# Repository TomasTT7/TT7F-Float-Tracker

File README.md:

# TT7F-Float-Tracker

This is the main repository for [TT7F high altitude balloon tracker](http://tt7hab.blogspot.cz/2016/08/the-tt7f-hardware.html).
It includes the board and schematic Eagle files and the current state of software that is continually being worked on.

The tracker is designed around Atmel's SAM3S8B microcontroller. It acquires the current position from Ublox MAX-M8Q GPS module. As a transmitter it uses Silicon Labs Si4060 to transmit in the 70cm and 2m bands. It is also equipped with a connector and an interface for MT9D111 camera module to provide [SSDV](https://ukhas.org.uk/guides:ssdv) (Slow Scan Digital Video) capability.

The power supply consists of TPS63031 buck-boost converter providing 3.3V to the MCU, GPS module and transmitter. The MT9D111 camera module is powered by two ME6211 LDO regulators (1.8V and 2.8V). The tracker is also capable of using LTC3105 MPPC converter in connection with a pair of solar cells to charge a battery (up to 4.2V) and power the TPS63031 converter.

For programming purposes it is equipped with a USB micro B interface which can provide power to the board via MCP1700 LDO regulator as well.

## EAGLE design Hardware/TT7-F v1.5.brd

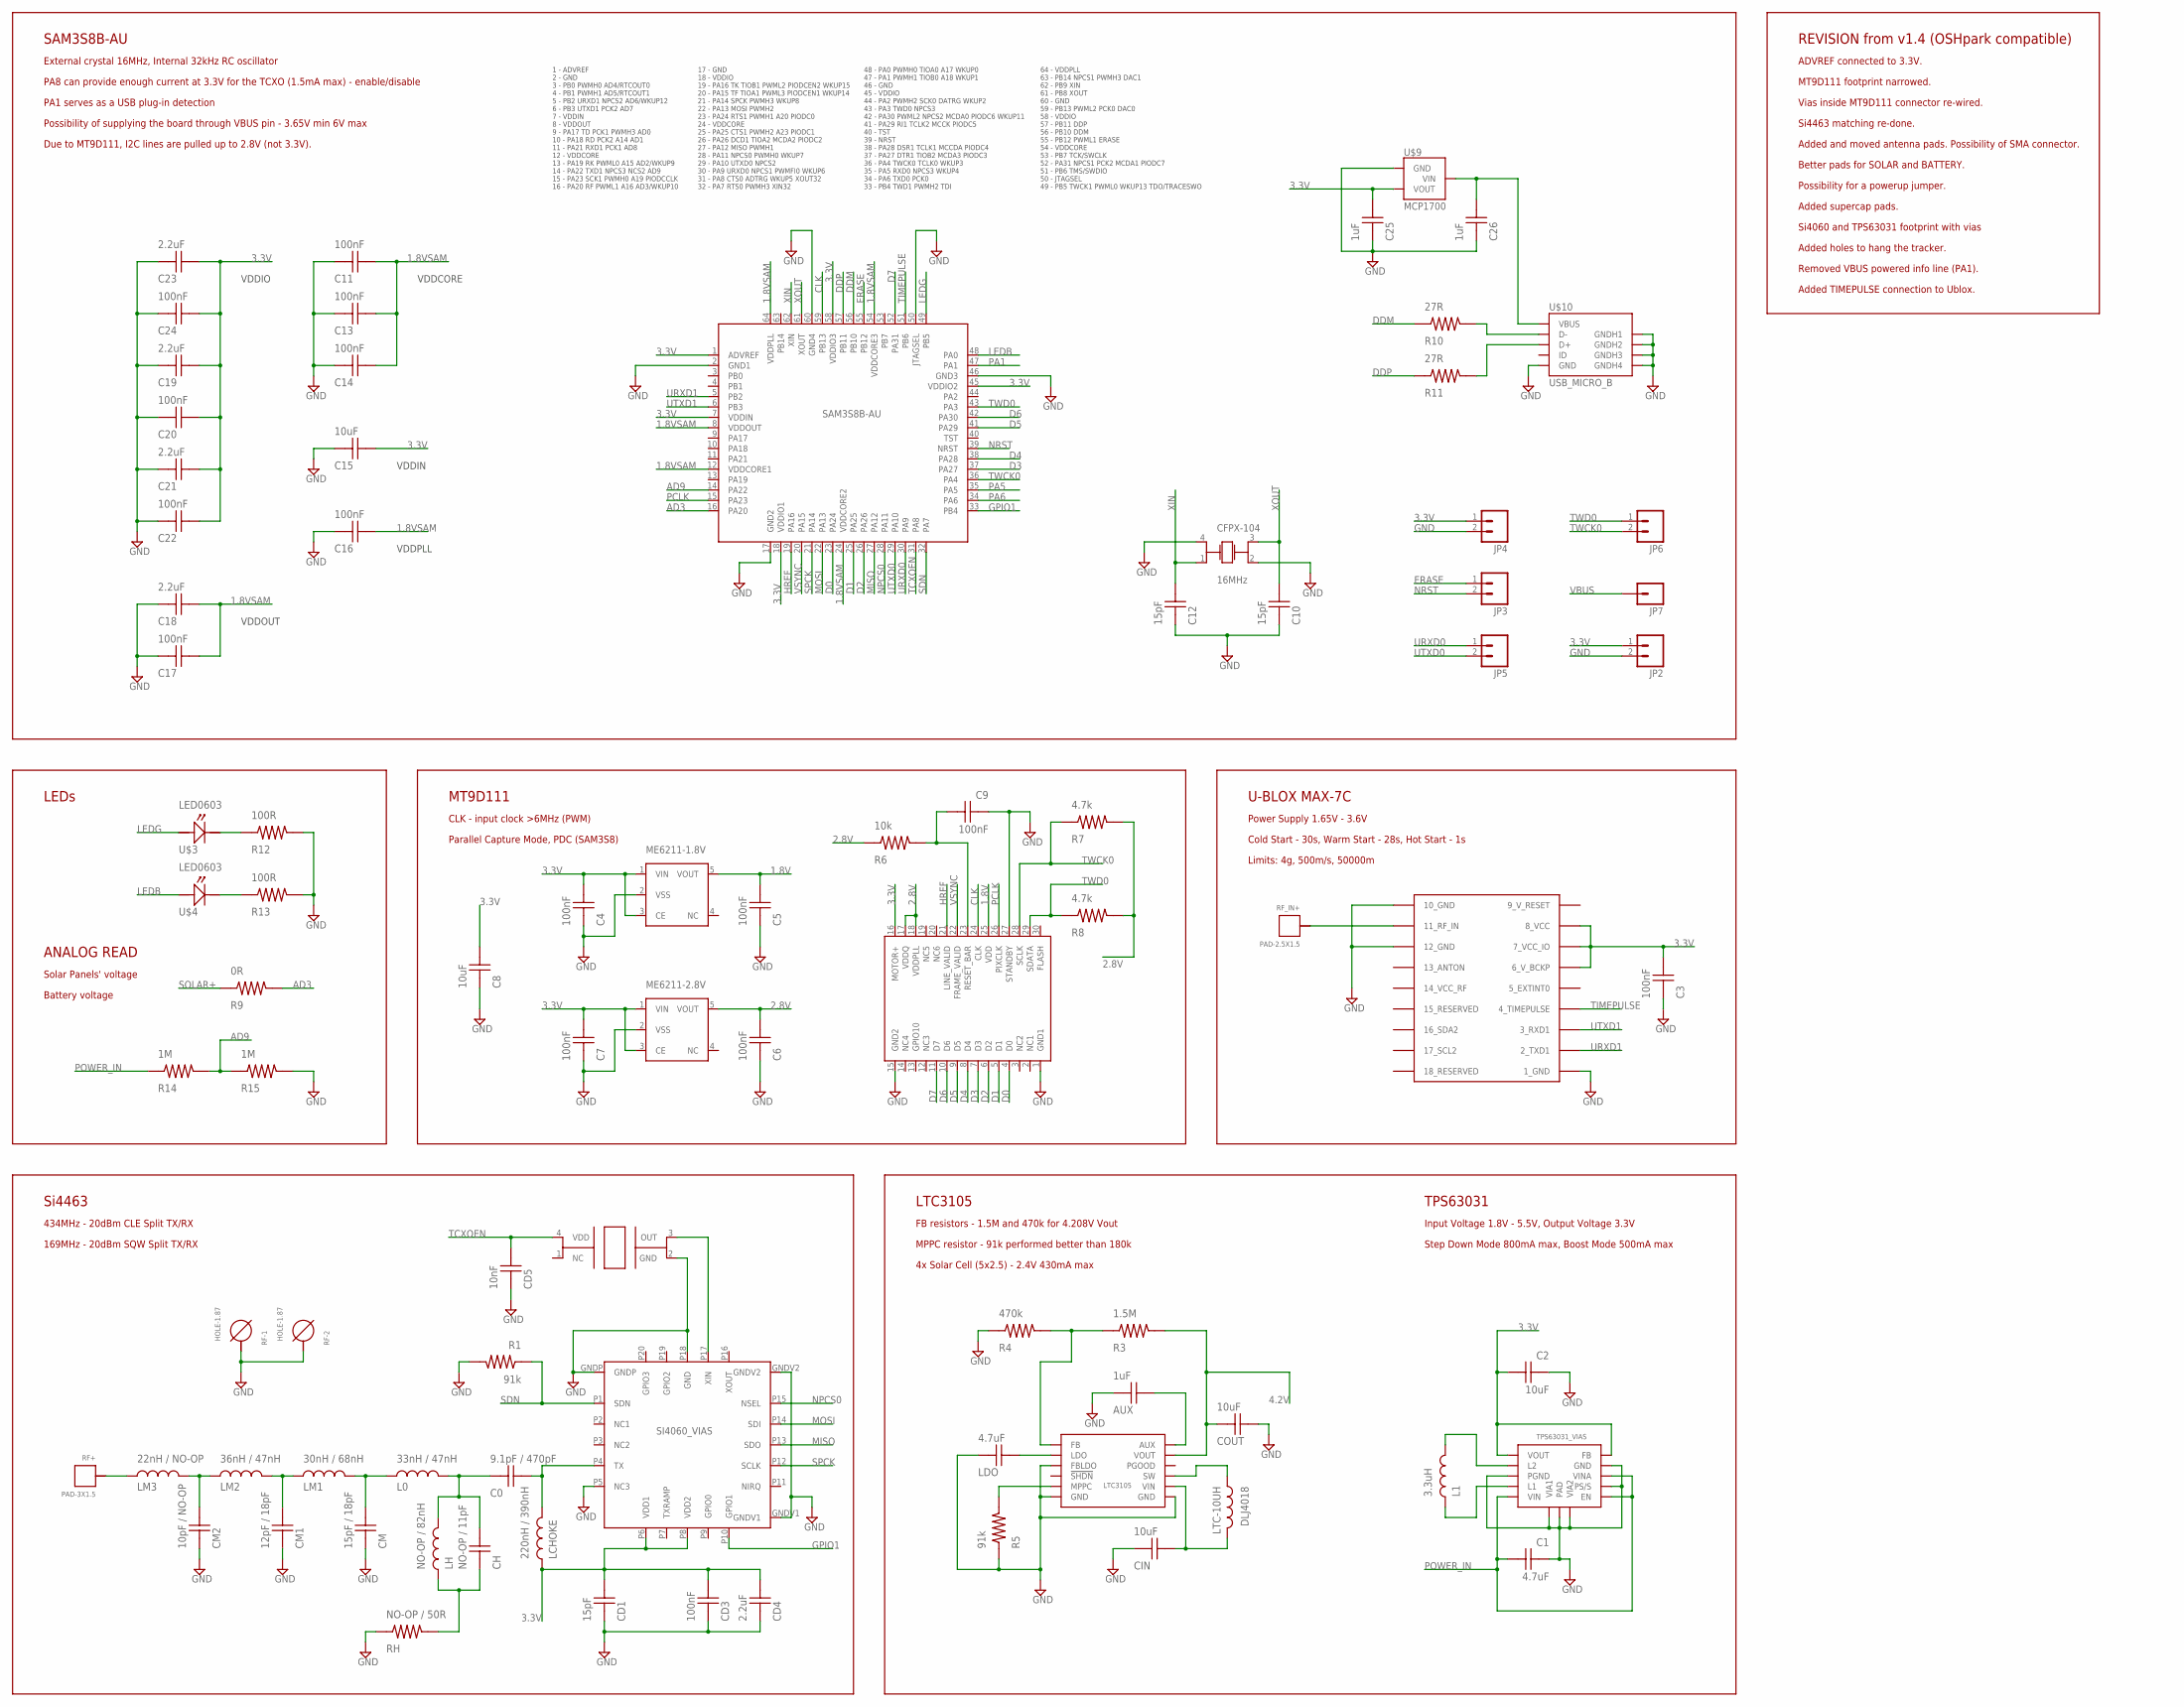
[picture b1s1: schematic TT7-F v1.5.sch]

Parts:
AUX: 1uF; CAP0603
C0: 9.1pF / 470pF; CAP0402
C1: 4.7uF; CAP0603
C2, C8: 10uF; CAP0805
C3, C4, C5, C6, C7, C9, C11, C13, C14, C16, C17, C20, C22, C24: 100nF; CAP0402
C10, C12: 15pF; CAP0402
C15: 10uF; CAP0603
C18, C19, C21, C23: 2.2uF; CAP0402
C25, C26: 1uF; CAP0603
CD1: 15pF; CAP0402
CD3: 100nF; CAP0402
CD4: 2.2uF; CAP0402
CD5: 10nF; CAP0402
CFPX-104: 16MHz; CFPX-104
CH: NO-OP / 11pF; CAP0402
CIN: 10uF; CAP0603
CM: 15pF / 18pF; CAP0402
CM1: 12pF / 18pF; CAP0402
CM2: 10pF / NO-OP; CAP0402
COUT: 10uF; CAP0805
JP2, JP3, JP4, JP5, JP6: M021X02_NO_SILK; 1X02_NO_SILK
JP7: M01PTH_NO_SILK_YES_STOP; 1X01_NO_SILK
L0: 33nH / 47nH; IND0402
L1: 3.3uH; DLJ3015
LCHOKE: 220nH / 390nH; IND0402
LDO: 4.7uF; CAP0603
LH: NO-OP / 82nH; IND0402
LM1: 30nH / 68nH; IND0402
LM2: 36nH / 47nH; IND0402
LM3: 22nH / NO-OP; IND0402
LTC-10UH: DLJ4018
ME6211-1.8V, ME6211-2.8V: ME6211_NEW
R1, R5: 91k; RES0402
R3: 1.5M; RES0402
R4: 470k; RES0402
R6: 10k; RES0402
R7, R8: 4.7k; RES0402
R9: 0R; RES0402
R10, R11: 27R; RES0402
R12, R13: 100R; RES0402
R14, R15: 1M; RES0603
RF+: PAD-3X1.5
RF-1, RF-2: HOLE-1.87
RF_IN+: PAD-2.5X1.5
RH: NO-OP / 50R; RES0402
TCXO: 32MHz; I547-2P3_TCXO
U1: LTC3105
U3: TPS63031_VIAS
U4: SAM3S8B-AU
U$1: SI4060_VIAS
U$2: UBLOX_MAX-7C
U$3, U$4: LED0603
U$9: MCP1700
U$10: USB_MICRO_B
U$15: MT9D111-AVX145602-NEW

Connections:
1.8V: C5.P$2, ME6211-1.8V.5 (VOUT), U$15.25 (VDD)
1.8VSAM: C11.P$2, C13.P$2, C14.P$2, C16.P$2, C17.P$2, C18.P$2, U4.8 (VDDOUT), U4.12 (VDDCORE1), U4.24 (VDDCORE2), U4.54 (VDDCORE3), U4.64 (VDDPLL)
2.8V: C6.P$2, ME6211-2.8V.5 (VOUT), R6.P$1, R7.P$2, R8.P$2, U$15.17 (VDDQ), U$15.18 (VDDPLL)
3.3V: C2.P$2, C3.P$2, C4.P$2, C7.P$2, C8.P$2, C15.P$2, C19.P$2, C20.P$2, C21.P$2, C22.P$2, C23.P$2, C24.P$2, C25.P$2, CD1.P$2, CD3.P$2, CD4.P$2, JP2.1, JP4.1, LCHOKE.P$1, ME6211-1.8V.1 (VIN), ME6211-1.8V.3 (CE), ME6211-2.8V.1 (VIN), ME6211-2.8V.3 (CE), U3.1 (VOUT), U3.10 (FB), U4.1 (ADVREF), U4.7 (VDDIN), U4.18 (VDDIO1), U4.45 (VDDIO2), U4.58 (VDDIO3), U$1.P6 (VDD1), U$1.P8 (VDD2), U$2.6_V_BCKP, U$2.7_VCC_IO, U$2.8_VCC, U$9.2 (VOUT), U$15.16 (MOTOR+)
4.2V: COUT.P$1, R3.P$2, U1.11 (VOUT)
9_V_RESET: U$2.9_V_RESET
AD3: R9.P$2, U4.16 (PA20)
AD9: R14.P$2, R15.P$1, U4.14 (PA22)
CLK: U4.59 (PB13), U$15.24 (CLK)
D0: U4.23 (PA24), U$15.4 (D0)
D1: U4.25 (PA25), U$15.5 (D1)
D2: U4.26 (PA26), U$15.6 (D2)
D3: U4.37 (PA27), U$15.7 (D3)
D4: U4.38 (PA28), U$15.8 (D4)
D5: U4.41 (PA29), U$15.9 (D5)
D6: U4.42 (PA30), U$15.10 (D6)
D7: U4.52 (PA31), U$15.11 (D7)
DDM: R10.P$1, U4.56 (PB10)
DDP: R11.P$1, U4.57 (PB11)
ERASE: JP3.1, U4.55 (PB12)
GND: AUX.P$1, C1.P$1, C2.P$1, C3.P$1, C4.P$1, C5.P$1, C6.P$1, C7.P$1, C8.P$1, C9.P$1, C10.P$1, C11.P$1, C12.P$1, C13.P$1, C14.P$1, C15.P$1, C16.P$1, C17.P$1, C18.P$1, C19.P$1, C20.P$1, C21.P$1, C22.P$1, C23.P$1, C24.P$1, C25.P$1, C26.P$1, CD1.P$1, CD3.P$1, CD4.P$1, CD5.P$1, CFPX-104.2 (GND1), CFPX-104.4 (GND2), CIN.P$1, CM.P$1, CM1.P$1, CM2.P$1, COUT.P$2, JP2.2, JP4.2, LDO.P$1, ME6211-1.8V.2 (VSS), ME6211-2.8V.2 (VSS), R1.P$2, R4.P$1, R5.P$1, R12.P$2, R13.P$2, R15.P$2, RF-1.P$1, RF-2.P$1, RH.P$1, TCXO.2 (GND), U1.3 (FBLDO), U1.6 (GND), U1.7 (GND), U3.3 (PGND), U3.7 (PS/S), U3.9 (GND), U3.11 (PAD), U3.VIA1, U3.VIA2, U4.2 (GND1), U4.17 (GND2), U4.46 (GND3), U4.50 (JTAGSEL), U4.60 (GND4), U$1.GNDP, U$1.GNDV1, U$1.GNDV2, U$1.P5 (NC3), U$1.P18 (GND), U$2.1_GND, U$2.10_GND, U$2.12_GND, U$9.1 (GND), U$10.GND, U$10.P$6 (GNDH1), U$10.P$7 (GNDH2), U$10.P$8 (GNDH3), U$10.P$9 (GNDH4), U$15.1 (GND1), U$15.15 (GND2), U$15.27 (STANDBY)
GPIO1: U4.33 (PB4), U$1.P10 (GPIO1)
HREF: U4.19 (PA16), U$15.21 (LINE_VALID)
LEDB: U4.48 (PA0), U$4.ANODE
LEDG: U4.49 (PB5), U$3.ANODE
MISO: U4.27 (PA12), U$1.P13 (SDO)
MOSI: U4.22 (PA13), U$1.P14 (SDI)
unnamed: CH.P$1, LH.P$1, RH.P$2
unnamed: C0.P$2, LCHOKE.P$2, U$1.P4 (TX)
unnamed: R12.P$1, U$3.CATHODE
unnamed: C0.P$1, CH.P$2, L0.P$2, LH.P$2
unnamed: CM.P$2, L0.P$1, LM1.P$2
unnamed: CM1.P$2, LM1.P$1, LM2.P$2
unnamed: CM2.P$2, LM2.P$1, LM3.P$2
unnamed: TCXO.3 (OUT), U$1.P17 (XIN)
unnamed: L1.P$1, U3.4 (L1)
unnamed: LTC-10UH.P$1, U1.9 (SW)
unnamed: LM3.P$1, RF+.P$1
unnamed: LDO.P$2, U1.2 (LDO)
unnamed: R5.P$2, U1.5 (MPPC)
unnamed: AUX.P$2, U1.12 (AUX)
unnamed: L1.P$2, U3.2 (L2)
unnamed: R3.P$1, R4.P$2, U1.1 (FB)
unnamed: RF_IN+.P$1, U$2.11_RF_IN
unnamed: R11.P$2, U$10.D+
unnamed: R10.P$2, U$10.D-
unnamed: C9.P$2, R6.P$2, U$15.23 (RESET_BAR)
unnamed: R13.P$1, U$4.CATHODE
NPCS0: U4.28 (PA11), U$1.P15 (NSEL)
NRST: JP3.2, U4.39 (NRST)
PA1: U4.47 (PA1)
PA5: U4.35 (PA5)
PA6: U4.34 (PA6)
PCLK: U4.15 (PA23), U$15.26 (PIXCLK)
POWER_IN: C1.P$2, R14.P$1, U3.5 (VIN), U3.6 (EN), U3.8 (VINA)
SDN: R1.P$1, U4.32 (PA7), U$1.P1 (SDN)
SOLAR+: CIN.P$2, LTC-10UH.P$2, R9.P$1, U1.8 (VIN)
SPCK: U4.21 (PA14), U$1.P12 (SCLK)
TCXOEN: CD5.P$2, TCXO.4 (VDD), U4.31 (PA8)
TIMEPULSE: U4.51 (PB6), U$2.4_TIMEPULSE
TWCK0: JP6.2, R7.P$1, U4.36 (PA4), U$15.28 (SCLK)
TWD0: JP6.1, R8.P$1, U4.43 (PA3), U$15.29 (SDATA)
URXD0: JP5.1, U4.30 (PA9)
URXD1: U4.5 (PB2), U$2.2_TXD1
UTXD0: JP5.2, U4.29 (PA10)
UTXD1: U4.6 (PB3), U$2.3_RXD1
VBUS: C26.P$2, JP7.1, U$9.3 (VIN), U$10.VBUS
VSYNC: U4.20 (PA15), U$15.22 (FRAME_VALID)
XIN: C12.P$2, CFPX-104.1 (XTAL1), U4.62 (XIN)
XOUT: C10.P$2, CFPX-104.3 (XTAL2), U4.61 (XOUT)

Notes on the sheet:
Si4463
434MHz - 20dBm CLE Split TX/RX
LTC3105
TPS63031
FB resistors - 1.5M and 470k for 4.208V Vout
MPPC resistor - 91k performed better than 180k
4x Solar Cell (5x2.5) - 2.4V 430mA max
Input Voltage 1.8V - 5.5V, Output Voltage 3.3V
Step Down Mode 800mA max, Boost Mode 500mA max
U-BLOX MAX-7C
Power Supply 1.65V - 3.6V
Cold Start - 30s, Warm Start - 28s, Hot Start - 1s
Limits: 4g, 500m/s, 50000m
MT9D111
SAM3S8B-AU
CLK - input clock >6MHz (PWM)
Parallel Capture Mode, PDC (SAM3S8)
LEDs
ANALOG READ
External crystal 16MHz, Internal 32kHz RC oscillator
Solar Panels' voltage
Battery voltage
VDDIO
VDDCORE
VDDIN
VDDPLL
VDDOUT
PA8 can provide enough current at 3.3V for the TCXO (1.5mA max) - enable/disable
PA1 serves as a USB plug-in detection
Possibility of supplying the board through VBUS pin - 3.65V min 6V max
Due to MT9D111, I2C lines are pulled up to 2.8V (not 3.3V).
ADVREF connected to 3.3V.
REVISION from v1.4 (OSHpark compatible)
MT9D111 footprint narrowed.
Vias inside MT9D111 connector re-wired.
Si4463 matching re-done.
Added and moved antenna pads. Possibility of SMA connector.
Better pads for SOLAR and BATTERY.
Possibility for a powerup jumper.
169MHz - 20dBm SQW Split TX/RX

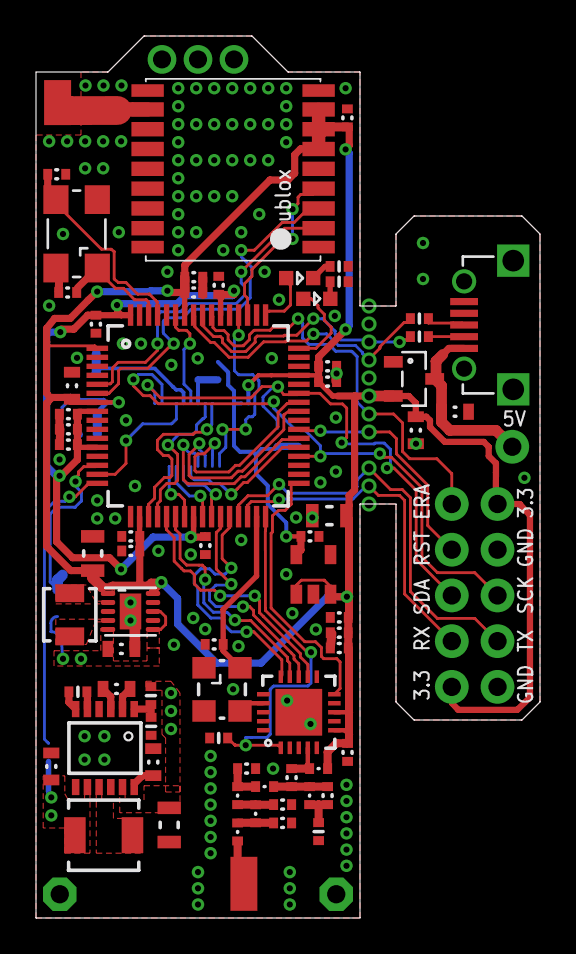
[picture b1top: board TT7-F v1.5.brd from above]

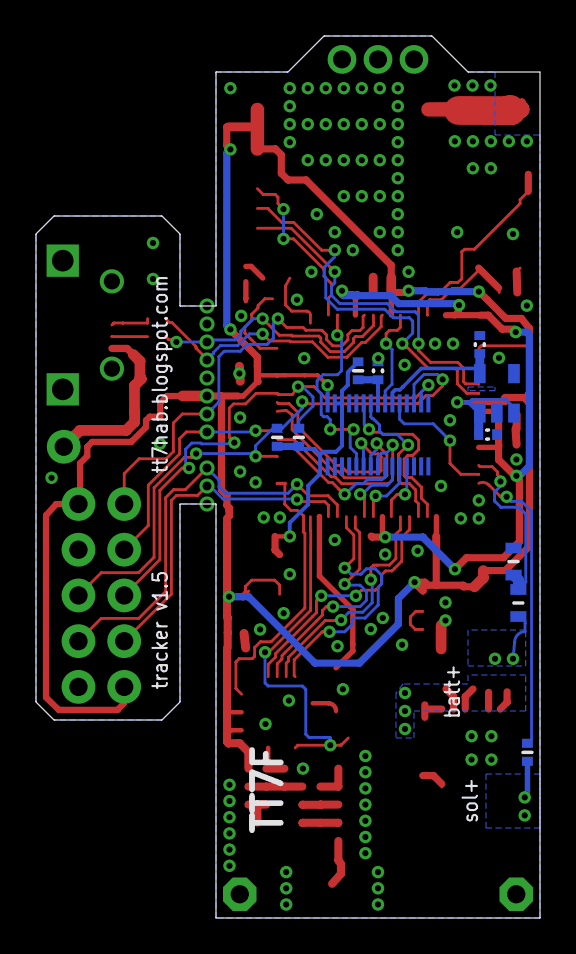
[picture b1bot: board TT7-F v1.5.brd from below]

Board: 2 copper layers, 28.0 x 49.0 mm, 86 parts (11 on the bottom side), 66 nets.

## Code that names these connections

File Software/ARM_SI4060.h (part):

/*
SI4060 AND SAM3S8 WIRING
	GPIO1		PB4
	SDN			PA7		(pull down to GND - active, when driven HIGH - shut down)
	TCXOEN		PA8		(drive HIGH to power the TCXO)
	NPCS0		PA11	(automatically HIGH when SPI enabled)
	MISO		PA12
	MOSI		PA13
	SPCK		PA14
*/

#ifndef ARM_SI4060_H
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void SI4060_CTS_check_and_read(uint8_t response_length);
void SI4060_init(void);
void SI4060_deinit(void);
void SI4060_setup_pins(uint8_t gpio0, uint8_t gpio1, uint8_t gpio2, uint8_t gpio3, uint8_t nirq, uint8_t sdo);
void SI4060_frequency(uint32_t freq);
void SI4060_frequency_fast(uint32_t freq);
void SI4463_tx_hop(uint32_t freq, uint16_t pll_settle_time);
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
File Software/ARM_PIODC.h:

/*
	Parallel Capture Mode - Peripheral D (PIO_ABCDSR1 - 1, PIO_ABCDSR2 - 1)
		PA15 - PIODCEN1
		PA16 - PIODCEN2
		PA23 - PIODCCLK
		PA24 - PIODC0
		PA25 - PIODC1
		PA26 - PIODC2
		PA27 - PIODC3
		PA28 - PIODC4
		PA29 - PIODC5
		PA30 - PIODC6
		PA31 - PIODC7

	-Enable PIOA peripheral clock
	-Configure the PDC
	-Configure the PIO Capture interrupt
	-Enable the PDC
	-Enable the PIO Capture
	-Wait for interrupt
	-Disable the interrupt
	-Read the DATA
*/


#ifndef ARM_PIODC_H
#define ARM_PIODC_H


#include "stdint.h"


// Functions
void PDC_transfer(uint8_t *buffer, uint16_t counter);
void PIOA_Handler(void);


#endif // ARM_PIODC_H_

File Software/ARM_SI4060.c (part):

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*/
void SI4060_init(void)
{
	// enable TCXO - PA8
	PMC->PMC_PCER0 |= (1 << ID_PIOA);			// enable clock to the peripheral
	PIOA->PIO_OER |= PIO_PA8;					// enable Output on PA8
	PIOA->PIO_PER |= PIO_PA8;					// enable PIO control on the pin (disable peripheral control)
	PIOA->PIO_PUDR |= PIO_PA8;					// disable pull-up
	PIOA->PIO_SODR |= PIO_PA8;					// Set Output Data Register
	
	// setup GPIO1 - PB4
	MATRIX->CCFG_SYSIO |= (1 << 4);				// System I/O lines must be configured in this register as well (PB4, PB5, PB6, PB7, PB10, PB11, PB12)
	PMC->PMC_PCER0 |= (1 << ID_PIOB);			// enable clock to the peripheral
	PIOB->PIO_OER |= PIO_PB4;					// enable Output on PB4
	PIOB->PIO_PER |= PIO_PB4;					// enable PIO control on the pin (disable peripheral control)
	PIOB->PIO_PUDR |= PIO_PB4;					// disable pull-up
	
	// setup SDN - PA7
	PIOA->PIO_OER |= PIO_PA7;					// enable Output on PA7
	PIOA->PIO_PER |= PIO_PA7;					// enable PIO control on the pin (disable peripheral control)
	PIOA->PIO_PUDR |= PIO_PA7;					// disable pull-up
	PIOA->PIO_SODR |= PIO_PA7;					// Set Output Data Register
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

/*
	Reset via SDN pin required to bring the transmitter to its original state (least consumption).
*/
void SI4060_deinit(void)
{
	SI4060_change_state(1);						// Sleep/Standby
	
	// de-init GPIO1 - PB4
	PIOB->PIO_ODR |= PIO_PB4;					// disable Output on PB4
	PIOB->PIO_PUER |= PIO_PB4;					// enable pull-up
	
	// de-init SDN - PA7
	PIOA->PIO_SODR |= PIO_PA7;					// Set Output Data Register
	SysTick_delay_ms(1);
	PIOA->PIO_CODR |= PIO_PA7;					// Clear Output Data Register
	PIOA->PIO_ODR |= PIO_PA7;					// disable Output on PA7
	
	// disable TCXO - PA8
	PIOA->PIO_CODR |= PIO_PA8;					// Clear Output Data Register
	PIOA->PIO_ODR |= PIO_PA8;					// disable Output on PA8
	PIOA->PIO_PUER |= PIO_PA8;					// enable pull-up
}

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/*
	GENERALLY
		GPIO0		0x02	disable pull-up, pin is configured as a CMOS output and driven low
		GPIO1		0x04	disable pull-up, pin is configured as a CMOS input (TXDATA input for TX Direct Mode)
		GPIO2		0x02	disable pull-up, pin is configured as a CMOS output and driven low
		GPIO3		0x02	disable pull-up, pin is configured as a CMOS output and driven low
		NIRQ		0x00	disable pull-up, behavior of this pin is not modified
		SDO			0x00	disable pull-up, behavior of this pin is not modified
		GEN_CONFIG	0x00	GPIOs configured as outputs will have the highest drive strength
*/
void SI4060_setup_pins(uint8_t gpio0, uint8_t gpio1, uint8_t gpio2, uint8_t gpio3, uint8_t nirq, uint8_t sdo)
{
	SPI_write(0x13, 0);							// GPIO_PIN_CFG
	SPI_write(gpio0, 0);						// GPIO0 - 0x02
	SPI_write(gpio1, 0);						// GPIO1 - 0x04 - pin is configured as a CMOS input
	SPI_write(gpio2, 0);						// GPIO2 - 0x02
	SPI_write(gpio3, 0);						// GPIO3 - 0x02
	SPI_write(nirq, 0);							// NIRQ - 0x00
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

/*
	DIRECT TX MODE the modulation is sourced in real-time from a GPIO1 pin.
	
	MOD:		CW 		0
				OOK 	1
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	SPI_write(0x20, 0);												// MODEM (group)
	SPI_write(0x01, 0);												// 1 (num_props)
	SPI_write(0x00, 0);												// MODEM_MOD_TYPE (start_prop)
	SPI_write(((syncasync << 7) | (1 << 5) | (1 << 3) | mod), 1);	// (data) GPIO1 as the source of data (INPUT), TX Direct Mode
	SI4060_CTS_check_and_read(0);
}

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	GFSK_SYNC
		TC0				26400Hz		(26400 interrupts per second)
		Baud Rate		1200		(every 22 interrupts)
		Slow Sine Wave	1200Hz		(1 full wave length per Baud) -> every 11 interrupts change of HIGH/LOW on PB4 to create a half of the full wave
		Fast Sine Wave	2200Hz		(1.83 wave length per Baud) -> every 6 interrupts change of HIGH/LOW on PB4 to create a half of the full wave
	
	LOOKUP
		TC0				1200Hz		Baud Rate
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		{
			if(APRS_GFSK_TC0 == 6 || APRS_GFSK_TC0 == 12 || APRS_GFSK_TC0 == 18 || APRS_GFSK_TC0 == 22)	// 2200Hz
			{
				if(PIOB->PIO_ODSR && PIO_PB4) PIOB->PIO_CODR |= PIO_PB4;								// Clear Output Data Register - Si4060's GPIO1
				else PIOB->PIO_SODR |= PIO_PB4;															// Set Output Data Register - Si4060's GPIO1
			}
		}else{
			if(APRS_GFSK_TC0 == 11 || APRS_GFSK_TC0 == 22)												// 1200Hz
			{
				if(PIOB->PIO_ODSR && PIO_PB4) PIOB->PIO_CODR |= PIO_PB4;								// Clear Output Data Register - Si4060's GPIO1
				else PIOB->PIO_SODR |= PIO_PB4;															// Set Output Data Register - Si4060's GPIO1
			}
		}
		
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	
	for(uint32_t x = 0; x < len; x++)
	{
		PIOB->PIO_CODR |= PIO_PB4;								// clear GPIO1 - START BIT
		SysTick_delay_ms(TXDELAY_RTTY);
		for(uint8_t i = 0; i < TXBITS; i++)						// TX CHARACTER (7 or 8 bits)
		{
			if(c & 0x01)
			{
				PIOB->PIO_SODR |= PIO_PB4;						// set GPIO1
		}else{
				PIOB->PIO_CODR |= PIO_PB4;						// clear GPIO1
			}
			SysTick_delay_ms(TXDELAY_RTTY);
			c = c >> 1;
		}
		PIOB->PIO_SODR |= PIO_PB4;								// set GPIO1 - STOP BIT
		SysTick_delay_ms(TXDELAY_RTTY);
		PIOB->PIO_SODR |= PIO_PB4;								// set GPIO1 - STOP BIT
		SysTick_delay_ms(TXDELAY_RTTY);
		c = *string++;
	}
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	
	for(uint32_t x = 0; x < len; x++)
	{
		PIOB->PIO_CODR |= PIO_PB4;								// clear GPIO1 - START BIT
		while(!(TC0->TC_CHANNEL[0].TC_SR & (0x01 << 4)));		// wait for CPCS flag - programmed delay
		for(uint8_t i = 0; i < TXBITS; i++)						// TX CHARACTER (7 or 8 bits)
		{
			if(c & 0x01)
			{
				PIOB->PIO_SODR |= PIO_PB4;						// set GPIO1
			}else{
				PIOB->PIO_CODR |= PIO_PB4;						// clear GPIO1
			}
			while(!(TC0->TC_CHANNEL[0].TC_SR & (0x01 << 4)));	// wait for CPCS flag - programmed delay
			c = c >> 1;
		}
		PIOB->PIO_SODR |= PIO_PB4;								// set GPIO1 - STOP BIT
		while(!(TC0->TC_CHANNEL[0].TC_SR & (0x01 << 4)));		// wait for CPCS flag - programmed delay
		PIOB->PIO_SODR |= PIO_PB4;								// set GPIO1 - STOP BIT
		while(!(TC0->TC_CHANNEL[0].TC_SR & (0x01 << 4)));		// wait for CPCS flag - programmed delay
		c = *string++;
	}
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
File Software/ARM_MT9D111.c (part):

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{
	PMC->PMC_PCER0 |= (1 << ID_PIOA);											// enable clock to the peripheral
	
	// disable PIOC control on the pin (disable peripheral control) - VSYNC, HREF, PCLK, D0, D1, D2, D3, D4, D5, D6, D7
	PIOA->PIO_PDR |= PIO_PA15 | PIO_PA16 | PIO_PA23 | PIO_PA24 | PIO_PA25 | PIO_PA26 | PIO_PA27 | PIO_PA28 | PIO_PA29 | PIO_PA30 | PIO_PA31;
	// disable pull-up - VSYNC, HREF, PCLK, D0, D1, D2, D3, D4, D5, D6, D7
	PIOA->PIO_PUDR |= PIO_PA15 | PIO_PA16 | PIO_PA23 | PIO_PA24 | PIO_PA25 | PIO_PA26 | PIO_PA27 | PIO_PA28 | PIO_PA29 | PIO_PA30 | PIO_PA31;
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
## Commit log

2016-10-13 Initial commit.
2016-10-19 Repaired APRS bit stuffing.
2016-10-19 .editorconfig
2016-10-22 Ublox tidied.
2016-10-28 Added WatchDog.
2016-10-30 Added EEFC.
2016-10-31 WATCHDOG repaired.
2016-11-01 SPI cleaning.
2016-11-08 Added GEOFENCE.
2016-11-09 Minor changes.
2016-11-09 Arrays declared static.
2016-11-09 Global APRS frequency.
2016-11-09 APRS cleanup.
2016-11-14 Added wkup12.
2016-11-14 Better de-init.
2016-11-14 Calibrated offset.
2016-11-14 Added Temp read.
2016-11-14 Enlarged telemetry and backlog.
2016-12-07 APRS modulation fine tuning.
2016-12-07 APRS flags.
2017-02-13 APRS address SSID updated.
2017-03-02 A number of updates.
2017-03-17 SystemInit update.
2017-03-17 MT9D111 and Ublox update.
2017-05-08 New version.
2017-05-12 XTAL prescaler.
2017-05-23 UBX messages update.
2017-06-22 TT7F1's main function.
2017-06-25 GPS fix timeout prolonged.
2017-06-25 Backlog SAM3S4B notes.
2017-07-01 TT7F2 main function.
2017-07-01 Added feedback from some functions.
2017-07-01 SystemInit moved.
2017-07-01 Added SSDVstatus to telemetry.
2017-07-07 Final parameters.
2017-07-13 TT7F4 main function.
2017-07-15 Modifiable callsign.
2017-07-15 Final code.
2017-07-19 Final main function.
2017-09-26 Si5351 and WSPR libraries added.
2017-09-26 Updated a couple of borders.
2017-09-26 Updated a couple of area borders.
2017-09-26 TWI speed and error handling.
2017-09-26 UART communication timeout added.
2017-09-28 UTC Date and Time of Day validity added.
2017-10-01 Final script.
2017-10-18 Added WSPR parsers.

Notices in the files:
parts and their libraries:
SparkFun-Connectors: Licensing: Creative Commons ShareAlike 4.0 International - https://creativecommons.org/licenses/by-sa/4.0
